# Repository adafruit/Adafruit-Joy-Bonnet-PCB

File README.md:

## Adafruit Joy Bonnet PCB

<a href="http://www.adafruit.com/products/3464"><br/>
Click here to purchase one from the Adafruit shop</a>

PCB files for the Adafruit Joy Bonnet for Raspberry Pi. Format is EagleCAD schematic and board layout
* http://www.adafruit.com/product/3464

### Description

Pocket-sized fun is the name of this game, with the Joy Bonnet – our most fun Bonnet ever (no we didn't even think that was possible, either!). This Bonnet fits perfectly on top of your Raspberry Pi Zero (any kind) and gives you adorable hand-held arcade controls. Once you install our script onto your Pi, the controls will act like a keyboard, for easy use with any emulator or media player.

Personally, we found this Bonnet to work best with RetroPie/EmulationStation. On a Pi Zero we could emulate NES and MAME game (our favorites!) but other emulators that don't require more than 1GHz speeds will work OK too, e.g. a N64 emulator won't work, it needs way more power!

Best of all, this Bonnet is fully assembled - no soldering at all is required. You may need to solder headers onto your Pi Zero (or use press-fit headers) but once that's done you're ready to rock. In theory you could also use this with a Pi A+ or B+/2/3 but it wouldn't be very hand-held.

### License

Adafruit invests time and resources providing this open source design, please support Adafruit and open-source hardware by purchasing products from [Adafruit](https://www.adafruit.com)!

Designed by Limor Fried/Ladyada for Adafruit Industries.

Creative Commons Attribution/Share-Alike, all text above must be included in any redistribution. See license.txt for additional details.

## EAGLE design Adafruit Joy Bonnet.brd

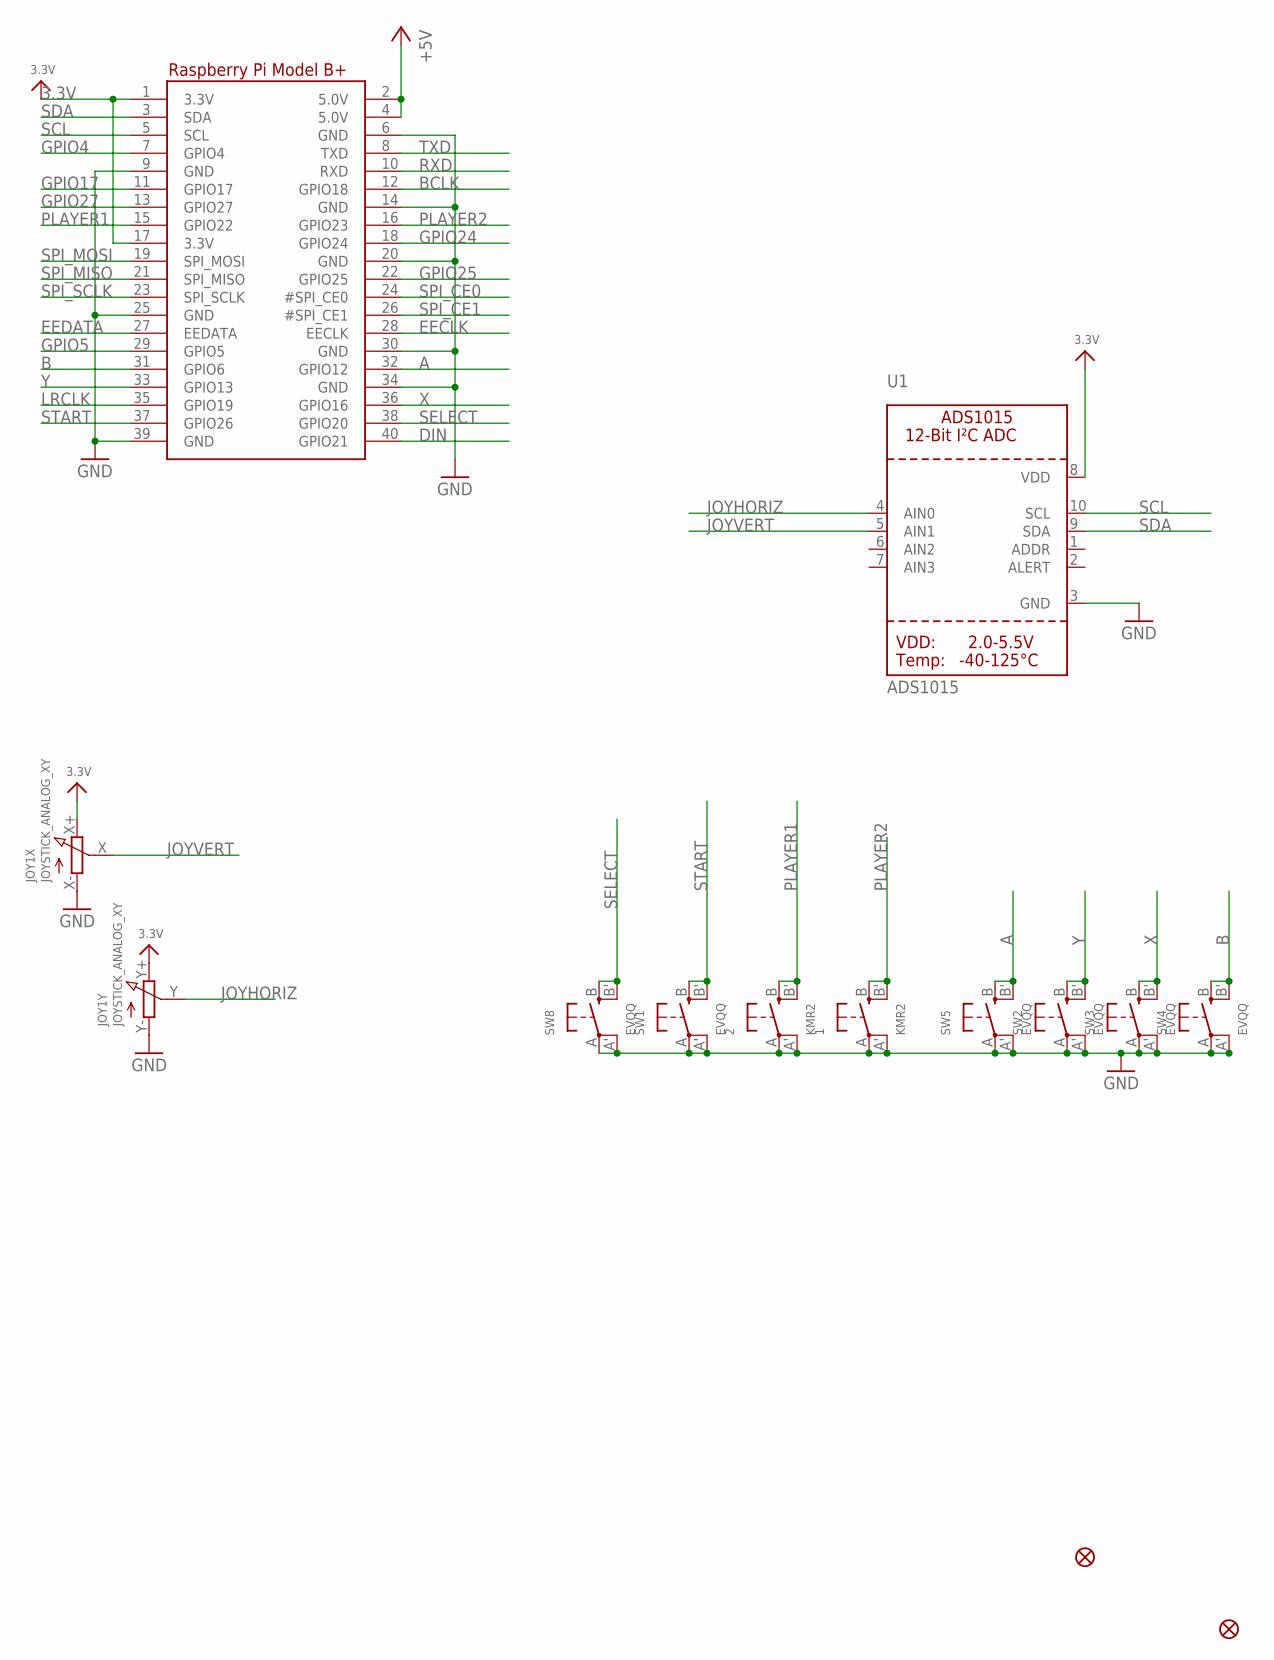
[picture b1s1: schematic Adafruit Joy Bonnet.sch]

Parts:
1, 2: KMR2; BTN_KMR2_4.6X2.8
FID2, FID3: FIDUCIAL_1MM
JOY1: JOYSTICK_ANALOG_XY; JOYSTICK_ANALOG_MINITHM
RPI1: RASPBERRYPI_BPLUS_BONNETSMT; PI_BONNET_SMT
SW1, SW2, SW3, SW4, SW5, SW8: EVQQ; EVQ-Q2_SMALLER
U1: ADS1015; MSOP10

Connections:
3.3V: JOY1.X+ (E), JOY1.Y+ (E), RPI1.1 (3.3V), RPI1.17 (3.3V), U1.8 (VDD)
+5V: RPI1.2 (5.0V), RPI1.4 (5.0V)
A: RPI1.32 (GPIO12), SW5.B (S), SW5.B' (S1)
B: RPI1.31 (GPIO6), SW4.B (S), SW4.B' (S1)
BCLK: RPI1.12 (GPIO18)
DIN: RPI1.40 (GPIO21)
EECLK: RPI1.28 (EECLK)
EEDATA: RPI1.27 (EEDATA)
GND: 1.A, 1.A' (P1), 2.A, 2.A' (P1), JOY1.X- (A), JOY1.Y- (A), RPI1.6 (GND), RPI1.9 (GND), RPI1.14 (GND), RPI1.20 (GND), RPI1.25 (GND), RPI1.30 (GND), RPI1.34 (GND), RPI1.39 (GND), SW1.A, SW1.A' (P1), SW2.A, SW2.A' (P1), SW3.A, SW3.A' (P1), SW4.A, SW4.A' (P1), SW5.A, SW5.A' (P1), SW8.A, SW8.A' (P1), U1.3 (GND)
GPIO4: RPI1.7 (GPIO4)
GPIO5: RPI1.29 (GPIO5)
GPIO17: RPI1.11 (GPIO17)
GPIO24: RPI1.18 (GPIO24)
GPIO25: RPI1.22 (GPIO25)
GPIO27: RPI1.13 (GPIO27)
JOYHORIZ: JOY1.Y (S), U1.4 (AIN0)
JOYVERT: JOY1.X (S), U1.5 (AIN1)
LRCLK: RPI1.35 (GPIO19)
PLAYER1: 2.B (S), 2.B' (S1), RPI1.15 (GPIO22)
PLAYER2: 1.B (S), 1.B' (S1), RPI1.16 (GPIO23)
RXD: RPI1.10 (RXD)
SCL: RPI1.5 (SCL), U1.10 (SCL)
SDA: RPI1.3 (SDA), U1.9 (SDA)
SELECT: RPI1.38 (GPIO20), SW8.B (S), SW8.B' (S1)
SPI_CE0: RPI1.24 (#SPI_CE0)
SPI_CE1: RPI1.26 (#SPI_CE1)
SPI_MISO: RPI1.21 (SPI_MISO)
SPI_MOSI: RPI1.19 (SPI_MOSI)
SPI_SCLK: RPI1.23 (SPI_SCLK)
START: RPI1.37 (GPIO26), SW1.B (S), SW1.B' (S1)
TXD: RPI1.8 (TXD)
X: RPI1.36 (GPIO16), SW3.B (S), SW3.B' (S1)
Y: RPI1.33 (GPIO13), SW2.B (S), SW2.B' (S1)

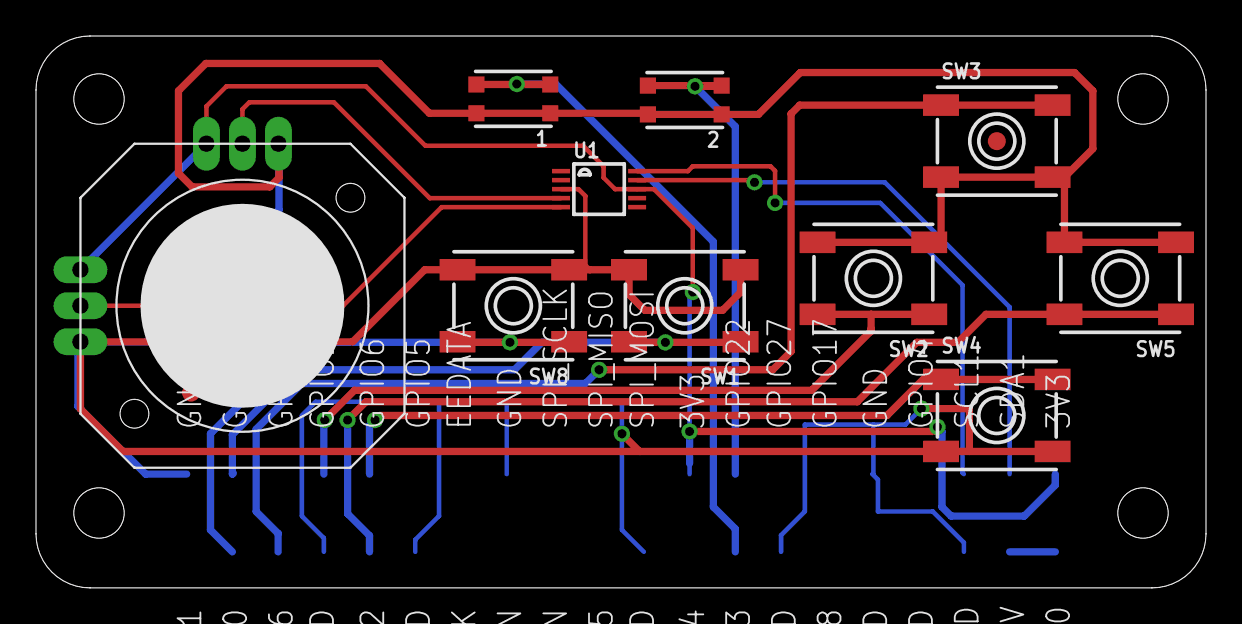
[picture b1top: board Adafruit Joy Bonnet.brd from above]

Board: 2 copper layers, 65.0 x 30.7 mm, 14 parts (1 on the bottom side), 15 nets.

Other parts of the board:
U$7: PCBFEAT-REV-040

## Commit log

2017-03-22 init!

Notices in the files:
parts and their libraries:
microbuilder: This work is placed in the public domain, and may be freely used for commercial and non-commercial work with the following conditions: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
